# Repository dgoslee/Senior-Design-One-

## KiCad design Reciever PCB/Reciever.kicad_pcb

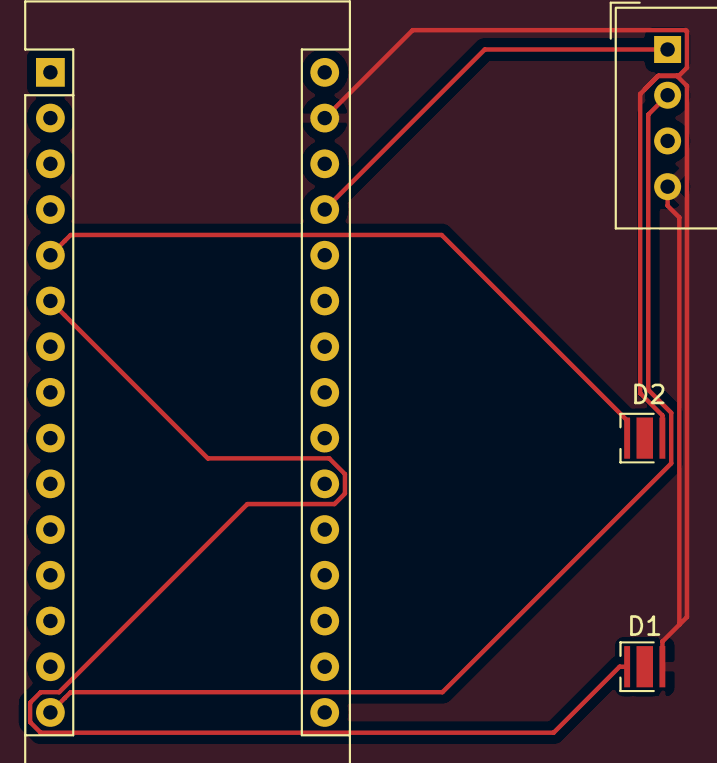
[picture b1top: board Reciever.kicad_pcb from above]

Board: 2 copper layers, 4 parts (0 on the bottom side), 5 nets.

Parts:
A1: Arduino_Nano_v2.x; Arduino_Nano
D1, D2: LED; LED_Cree-XB
U1: DHT11; Aosong_DHT11_5.5x12.0_P2.54mm

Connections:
unnamed: A1.5, D2.1
unnamed: A1.6, D1.1
unnamed: A1.15, U1.2
unnamed: A1.27, U1.1
unnamed: A1.29, D1.2, D2.2, U1.4

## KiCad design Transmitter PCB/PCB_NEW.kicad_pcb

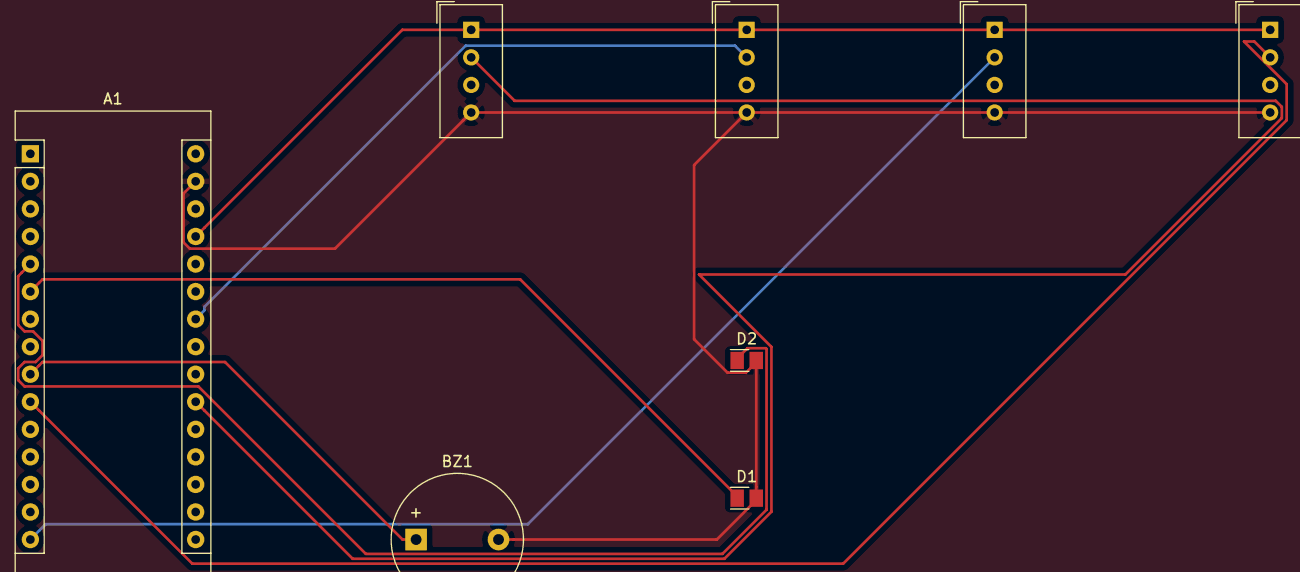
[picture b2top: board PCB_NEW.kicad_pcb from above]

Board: 2 copper layers, 8 parts (0 on the bottom side), 9 nets.

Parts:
A1: Arduino_Nano_v3.x; Arduino_Nano
BZ1: Buzzer; Buzzer_12x9.5RM7.6
D1, D2: LED; LED_Cree-XQ_HandSoldering
U1, U2, U3, U4: DHT11; Aosong_DHT11_5.5x12.0_P2.54mm

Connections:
unnamed: A1.5, D2.1
unnamed: A1.6, D1.1
unnamed: A1.9, BZ1.1
unnamed: A1.10, U4.2
unnamed: A1.15, U3.2
unnamed: A1.21, U1.2
unnamed: A1.24, U2.2
unnamed: A1.27, U1.1, U2.1, U3.1, U4.1
unnamed: A1.29, BZ1.2, D1.2, D2.2, U1.4, U2.4, U3.4, U4.4

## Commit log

2019-03-25 Arduino Code
    All head files, cpp files, and project code.
2019-04-04 Report and Power Point Update
2019-04-04 Updated Report
2019-12-07 Power Point
